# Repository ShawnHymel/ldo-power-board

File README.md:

# LDO Power Board

All design files were created using KiCad v5.1.

Feel free to modify this design for your own applciation. This PCB is intended to A) test your QFN soldering abilities and B) provide 3 power outputs on a breadboard project.

## License

Schematic and PCB layout files are licensed under the [CC BY 4.0](https://creativecommons.org/licenses/by/2.0/) license.

THE DESIGN IS PROVIDED "AS IS" AND THE AUTHOR DISCLAIMS ALL WARRANTIES WITH REGARD TO THIS DESIGN INCLUDING ALL IMPLIED WARRANTIES OF MERCHANTABILITY AND FITNESS. IN NO EVENT SHALL THE AUTHOR BE LIABLE FOR ANY SPECIAL, DIRECT, INDIRECT, OR CONSEQUENTIAL DAMAGES OR ANY DAMAGES WHATSOEVER RESULTING FROM LOSS OF USE, DATA OR PROFITS, WHETHER IN AN ACTION OF CONTRACT, NEGLIGENCE OR OTHER TORTIOUS ACTION, ARISING OUT OF OR IN CONNECTION WITH THE USE OR PERFORMANCE OF THIS DESIGN.

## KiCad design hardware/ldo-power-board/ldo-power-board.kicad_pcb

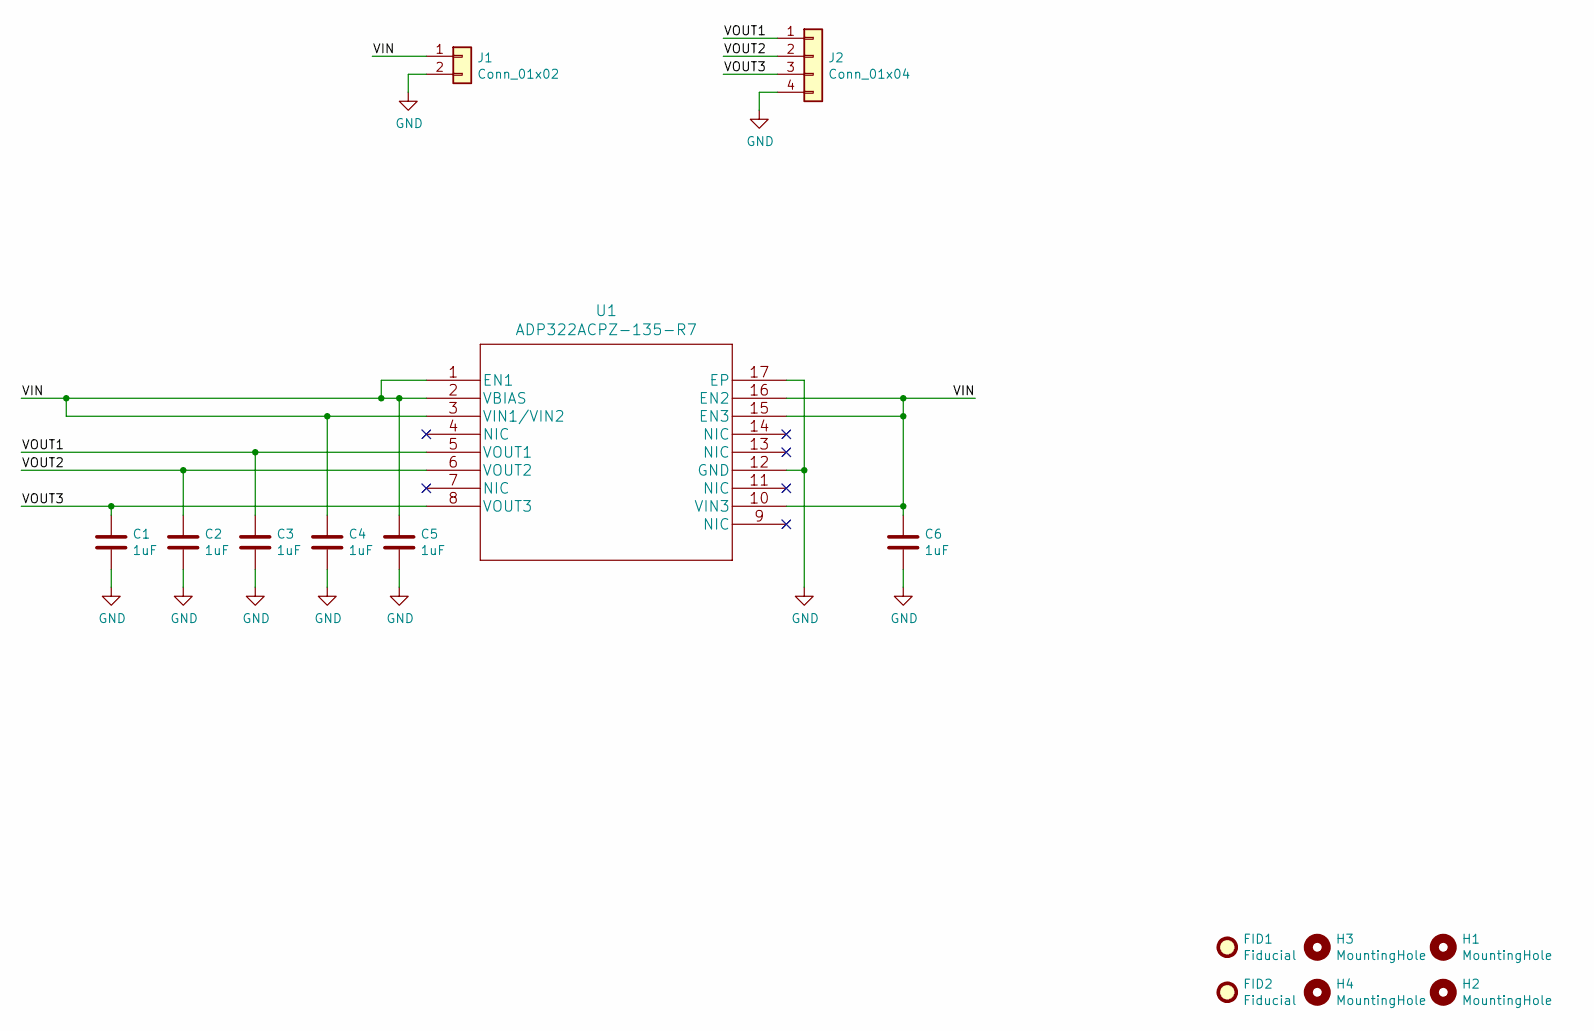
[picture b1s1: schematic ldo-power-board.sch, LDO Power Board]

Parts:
C1, C2, C3, C4, C5, C6: 1uF; C_0603_1608Metric_Pad1.08x0.95mm_HandSolder; Digi-Key_PN 1276-6524-1-ND
FID1, FID2: Fiducial; Fiducial_1mm_Mask2mm
H1, H2, H3, H4: MountingHole; MountingHole_2.1mm
J1: Conn_01x02; PinHeader_1x02_P2.54mm_Vertical
J2: Conn_01x04; PinHeader_1x04_P2.54mm_Vertical
U1: ADP322ACPZ-135-R7; Digi-Key_PN ADP322ACPZ-135-R7CT-ND

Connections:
/VIN: C4.1, C5.1, C6.1, J1.1, U1.1 (EN1), U1.2 (VBIAS), U1.3 (VIN1/VIN2), U1.10 (VIN3), U1.15 (EN3), U1.16 (EN2)
/VOUT1: C3.1, J2.1, U1.5 (VOUT1)
/VOUT2: C2.1, J2.2, U1.6 (VOUT2)
/VOUT3: C1.1, J2.3, U1.8 (VOUT3)
GND: C1.2, C2.2, C3.2, C4.2, C5.2, C6.2, J1.2, J2.4, U1.12 (GND), U1.17 (EP)

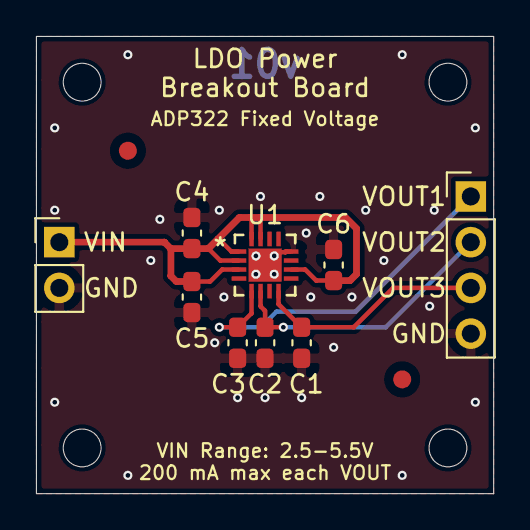
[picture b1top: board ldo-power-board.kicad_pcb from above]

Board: 2 copper layers, 25.4 x 25.4 mm, 15 parts (0 on the bottom side), 5 nets.

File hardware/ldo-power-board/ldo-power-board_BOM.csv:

Reference, Quantity, Value, Footprint, Datasheet, Digi-Key_PN
C1 C2 C3 C4 C5 C6 ,6,"1uF","Capacitor_SMD:C_0603_1608Metric_Pad1.08x0.95mm_HandSolder","~","1276-6524-1-ND"
FID1 FID2 ,2,"Fiducial","Fiducial:Fiducial_1mm_Mask2mm","~"
H1 H2 H3 H4 ,4,"MountingHole","MountingHole:MountingHole_2.1mm","~"
J1 ,1,"Conn_01x02","Connector_PinHeader_2.54mm:PinHeader_1x02_P2.54mm_Vertical","~"
J2 ,1,"Conn_01x04","Connector_PinHeader_2.54mm:PinHeader_1x04_P2.54mm_Vertical","~"
U1 ,1,"ADP322ACPZ-135-R7","adp322acpz:ADP322ACPZ-135-R7","","ADP322ACPZ-135-R7CT-ND"

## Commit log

2021-05-28 Schematic done
2021-05-29 Done with da layout

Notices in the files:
hardware/ldo-power-board/ldo-power-board.kicad_pcb:
License: CC BY 4.0
hardware/ldo-power-board/ldo-power-board.sch:
https://creativecommons.org/licenses/by/4.0
parts and their libraries:
Copyright 2016 Accelerated Designs. All rights reserved.
